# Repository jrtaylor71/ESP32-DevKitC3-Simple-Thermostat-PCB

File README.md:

# ESP32-S3-Simple-Thermostat

A comprehensive, feature-rich simple thermostat system built on the ESP32 platform with professional PCB design. Perfect for DIY smart home automation with full Home Assistant integration.

## 🌟 Key Features

- **📱 Local Touch Control**: ILI9341 TFT LCD with intuitive touch interface
- **🏠 Smart Home Ready**: Full MQTT integration with Home Assistant auto-discovery and climate entity support
- **📅 Bidirectional Schedule Sync**: 7-day schedules with day/night periods, HA helper automation, and live two-way update flow
- **🌡️ Multiple Sensors**: AHT20/BME280 ambient temperature and humidity plus DS18B20 hydronic water sensing
- **⚡ Multi-Stage HVAC**: Support for 2-stage heating and cooling, stage timing, delta thresholds, and stage 2 runtime logic
- **🌍 Regional HVAC Behavior**: Switchable US mode (standard temperature-driven cooling) or EU mode (adds optional humidity-driven dehumidification support alongside temperature control)
- **🔄 Heat Pump Ready**: Reversing valve support and heat-pump-compatible staging logic
- **🔥 Backup Heat Monitoring**: Auxiliary heat fallback logic with delay windows and temperature-drop detection
- **💨 Advanced Fan Control**: Auto, continuous, and scheduled cycling modes with independent heat/cool fan relay requirements
- **🔥 Separate Heat/Cool Fan Logic**: Configure whether the fan relay is needed for heating, cooling, or both for legacy HVAC systems
- **🧯 Hydronic Safety Protection**: DS18B20 water monitoring with lockout logic that blocks unsafe fan/heating operation and protects radiant systems
- **🚿 Shower Mode**: Pause heating for 5-120 minutes with countdown timer and buzzer alert
- **🌤️ Weather Integration**: OpenWeatherMap and Home Assistant weather with color-coded icons, current conditions, and display updates
- **🏢 Multi-Thermostat Support**: Scale from single-device installs to multi-device Home Assistant automation setups
- **🌐 Modern Web Interface**: Complete tabbed interface with embedded scheduling, status monitoring, OTA upload, and settings management
- **📡 Offline Operation**: Full functionality without WiFi connection or internet access
- **🔧 Professional PCB**: Custom PCB design for clean, permanent installation and compact integration
- **🔄 OTA Updates**: Over-the-air firmware updates with real-time progress tracking and reboot recovery
- **🔒 Factory Reset**: Built-in reset capability via boot button for clean default recovery
- **🎭 Motion Detection**: LD2410 24GHz mmWave sensor for automatic display wake and occupancy-aware screen behavior
- **🔊 Audible Alerts**: Buzzer feedback for shower mode, relay events, and user interaction cues
- **🧠 Reliability Features**: Watchdog reset, anti-flicker display refresh, I2C protection, and graceful sensor recovery

## �️ Operating Modes

### Thermostat Modes
- **Off**: All heating, cooling, and fan demand relays are disabled
- **Heat**: Single heat setpoint with configurable swing (hysteresis) to prevent short-cycling
- **Cool**: Single cool setpoint with configurable swing (hysteresis) to prevent short-cycling
- **Auto**: Single setpoint with a wider dead-zone swing; heating and cooling only activate once the temperature moves outside the dead-zone and turn off at the setpoint boundary rather than immediately on dead-zone re-entry

### Fan Modes
- **Auto**: Fan runs only when heating or cooling demand is active, based on the independent heat/cool fan relay requirement settings
- **On**: Fan runs continuously regardless of HVAC demand
- **Cycle**: Fan runs on a repeating schedule (configurable minutes per hour) even without active heating or cooling demand

### Regional HVAC Modes
- **US Mode**: Standard temperature-driven heating and cooling control
- **EU Mode**: Adds an optional humidity-driven dehumidification assist that runs alongside temperature control, using a configurable humidity setpoint, deadband, and dedicated relay selection

### Schedule Modes
- **Scheduled**: Setpoints automatically follow the active day/night period for the current day of week
- **Manual Override**: Adjusting a setpoint while a schedule is active temporarily overrides the schedule for a fixed duration before resuming normal scheduled behavior
- **Disabled**: Schedule following can be turned off entirely in favor of fixed manual setpoints

### Shower Mode
- Temporarily pauses heating for a configurable duration (5-120 minutes)
- Displays a live countdown timer on the touch screen while active
- Buzzer alert signals when the countdown is about to end
- Can be toggled directly from the touch screen setpoint control when enabled in settings

## �🚀 Quick Start

 - PCB V1.x

 - PCB V3.x

### Hardware Requirements
- ESP32-S3-WROOM-1-N16 (16MB Flash, No PSRAM) or N8/N32 variants
- ILI9341 320x240 TFT LCD with XPT2046 Touch Controller
- AHT20 or BME280 Temperature/Humidity Sensor (I2C)
- DS18B20 Temperature Sensor (optional, for hydronic heating)
- LD2410 24GHz mmWave Motion Sensor (optional, for display wake)
- 5x Relay Module for HVAC control
- Custom PCB that can use either onboard relay or external relays via pin header

### Software Setup

#### Option 1: Use Prebuilt Firmware (Recommended)
1. Clone this repository
2. Navigate to `firmware/` directory
3. Find the latest build folder (e.g., `build_YYYYMMDD-HHMMSS/`)
4. Flash using the variant-specific script:
   - **Linux/Mac**: 
     - Default: `./latest_flash_N16.sh` (uses /dev/ttyACM0)
     - Custom port: `./latest_flash_N16.sh /dev/ttyUSB0`
   - **Windows**: 
     - Default: `latest_flash_N16.bat` (uses COM3)
     - Custom port: `latest_flash_N16.bat COM4`
5. Use touch interface to configure WiFi and settings

#### Option 2: Build from Source
1. Install [PlatformIO](https://platformio.org/) IDE
2. Clone this repository
3. Open project in PlatformIO
4. Build firmware using `./build.sh` with options:
   - **Interactive mode**: `./build.sh` (select from menu)
   - **Specific variant**: `./build.sh 1` (N8), `./build.sh 2` (N16), or `./build.sh 3` (N32)
   - **All variants**: `./build.sh all` or `./build.sh 4`
   - **Additional flags**: `clean`, `quiet`, `cleanlibs`
   - **Examples**: 
     - `./build.sh 2` - Build 16MB variant (default)
     - `./build.sh all clean` - Clean build all variants
     - `./build.sh 3 quiet` - Build 32MB silently
     - `./build.sh cleanlibs` - Remove all libraries and packages
5. Memory usage: RAM 25.2% (82728/327680 bytes); Flash 19.0% (1246KB/6553KB for N16)
6. Firmware organized in `firmware/N8/`, `firmware/N16/`, `firmware/N32/` directories
7. Flash using variant-specific scripts:
   - **Linux/Mac**: 
     - Default: `./firmware/latest_flash_N16.sh` (uses /dev/ttyACM0)
     - Custom port: `./firmware/latest_flash_N16.sh /dev/ttyUSB0`
   - **Windows**: 
     - Default: `firmware\latest_flash_N16.bat` (uses COM3)
     - Custom port: `firmware\latest_flash_N16.bat COM5`
8. Use touch interface to configure WiFi and settings

#### Flashing Requirements
- **esptool.py** (installed automatically with PlatformIO)
- **USB connection** to ESP32-S3
- **Boot mode**: Hold BOOT button while connecting USB (if needed)
- **Default serial port**: `/dev/ttyACM0` (Linux/Mac) or `COM3` (Windows)

#### Manual Flashing with esptool

If you need to flash manually using esptool, use the following command:

**Linux/Mac:**
```bash
esptool.py --chip esp32s3 --port /dev/ttyACM0 --baud 460800 --before default_reset --after hard_reset write_flash -z \
    --flash_mode dio --flash_freq 80m --flash_size 16MB \
    0x0 bootloader.bin \
    0x8000 partitions.bin \
    0x10000 firmware.bin
```

**Windows:**
```bash
esptool.py --chip esp32s3 --port COM3 --baud 460800 --before default_reset --after hard_reset write_flash -z \
    --flash_mode dio --flash_freq 80m --flash_size 16MB \
    0x0 bootloader.bin \
    0x8000 partitions.bin \
    0x10000 firmware.bin
```

**Flash addresses for the 3 required files:**
- `bootloader.bin` at address `0x0`
- `partitions.bin` at address `0x8000`
- `firmware.bin` at address `0x10000`

**Adjust for your hardware:**
- Change `--port` to your serial port (Linux: `/dev/ttyACM0` or `/dev/ttyUSB0`, Windows: `COM3`, `COM4`, etc.)
- Change `--flash_size` to `8MB`, `16MB`, or `32MB` to match your ESP32-S3 variant (N8, N16, or N32)

For detailed build and flash instructions, see [USER_MANUAL.md](USER_MANUAL.md)

## 💻 Web Interface

Access the thermostat's web interface by navigating to its IP address:

### Tabbed Interface with Embedded Features

**Status Tab**: Real-time monitoring of:
- Current temperature and humidity
- Thermostat and fan modes
- Relay states and system status
- Weather information (when configured)
- Barometric pressure (with BME280 sensor)

**Settings Tab**: Complete configuration interface for:

- Temperature setpoints and control modes
- MQTT/Home Assistant integration and broker settings
- WiFi network settings and reboot recovery
- Multi-stage HVAC parameters including stage 2 runtime and delta thresholds
- Reversing valve configuration for heat-pump systems
- Backup heat enablement, relay selection, delay timing, and temperature-drop logic
- Hydronic heating controls with low/high water protection thresholds
- Fan scheduling options and independent heat/cool fan relay toggles
- Regional HVAC mode selection for US or EU behavior
- EU humidity dehumidification controls, relay selection, setpoint, and deadband
- Shower mode enable/disable and duration (5-120 minutes)
- Display brightness, sleep, and clock settings
- Temperature/humidity sensor calibration and offsets
- OTA update management and firmware details

**Schedule Tab**: Comprehensive 7-day scheduling:
- Day and night periods for each day of the week
- Editable Heat, Cool, and Auto temperatures for each period
- Time controls for period transitions
- Schedule enable/disable and override controls
- All options always visible - no hidden menus

**Weather Tab**: Weather data configuration:
- OpenWeatherMap API integration
- Home Assistant weather entity integration
- Configurable update intervals (5-60 minutes)
- City/state/country configuration

**System Tab**: Device information and firmware updates:
- System information and uptime
- Firmware version details
- OTA firmware upload with progress tracking
- Reboot and factory reset options

For complete usage instructions, see [USER_MANUAL.md](USER_MANUAL.md)

## 🏠 Home Assistant Integration

### Automatic Discovery & Control
Automatic discovery and integration with Home Assistant:

1. Enable MQTT in thermostat settings
2. Configure MQTT broker details
3. Thermostat appears automatically in Home Assistant with a full climate entity and status payloads
4. Full control via Home Assistant interface
5. Supports climate entity with heating, cooling, auto, and off modes
6. Publishes relay, mode, target, schedule override, and hydronic state for automation use

### Bidirectional Schedule Sync 🔄
Full synchronization between thermostat and Home Assistant:

**Device → HA (Inbound)**: 
- Thermostat publishes complete schedule on boot and config changes
- HA automations automatically update helper entities for each day and period
- Changes made on device instantly visible in HA

**HA → Device (Outbound)**:
- Change any schedule helper in HA (time, temperature, enabled status)
- Automation publishes change to device via MQTT immediately
- Device receives and applies change instantly
- No manual sync needed - fully automatic bidirectional flow

**Multi-Thermostat Support**:
- Each device gets its own set of helpers (shop_thermostat, studio_thermostat, house_thermostat, etc.)
- Centralized multi-device automation handles all thermostats
- Proper hostname normalization for MQTT topics vs. helper IDs
- Can manage 10+ thermostats from single HA instance

**Setup Instructions**:
1. Ensure MQTT is enabled on thermostat
2. Copy `multi_thermostat_schedule_sync.yaml` to HA packages directory
3. Generate per-device packages: `./generate_schedule_package.sh shop_thermostat`
4. Add package to HA configuration
5. Reload automations/scripts in HA
6. Helpers auto-populate from device schedule state

## 🛠️ Advanced Features

### Multi-Stage Operation
- Intelligent staging based on time and temperature
- Configurable stage 2 activation parameters and runtime thresholds
- Prevents system short-cycling and optimizes energy efficiency
- Supports separate heating and cooling stage logic for multi-stage HVAC systems
- Includes runtime gating and dead-zone control behavior for stable operation

### US/EU Regional HVAC Behavior
- Thermostat region mode can be configured for US or EU control behavior
- **US Mode**: Standard temperature-driven heating and cooling control
- **EU Mode**: Adds optional humidity-driven dehumidification assist that runs alongside temperature control, with configurable setpoint and deadband
- Standalone dehumidification state is surfaced to web status and TFT display
- Works with relay selection modes for cooling stage 1, stage 2, or pump relay output

### Heat Pump and Backup Heat Support
- Reversing valve support for heat-pump systems with mode-aware valve control
- Backup heat logic can monitor a primary heat source and automatically add auxiliary heat when recovery stalls or temperature falls too quickly
- Relay conflicts are automatically managed so backup heat does not overlap with reserved stage 2 or reversing valve outputs
- Works alongside standard heating and cooling staging without forcing a single control strategy

### Hydronic Heating Support
- DS18B20 water temperature monitoring
- Safety interlocks prevent operation when water is too cold
- Configurable high/low temperature thresholds
- Hydronic lockout logic blocks unsafe heating/fan behavior when the loop is below the configured minimum
- Perfect for radiant floor heating systems and hydronic boiler setups

### Fan Control Options
- **Auto**: Fan runs only with heating/cooling
- **On**: Continuous fan operation
- **Cycle**: Scheduled fan operation (configurable minutes per hour)
- **Independent Heat/Cool Relay Settings**: Choose whether a fan relay is required while heating, while cooling, or for both modes
- **Legacy HVAC Compatibility**: Supports systems where the fan is required for cooling only, heating only, or both without forcing a single global setting

### Display, Sensor, and Safety Enhancements
- Motion-based wake on LD2410 radar occupancy detection
- Display sleep and dimming support with activity sensing
- Buzzer feedback for alerts, boot tones, and mode transitions
- Watchdog protection, OTA recovery, and factory reset support
- AHT20/BME280 temperature/humidity calibration offsets and sensor error recovery
- I2C mutex protection to prevent bus contention between sensors and display logic
- Anti-flicker display refresh logic and stable UI updates
- Hydronic low-temp alert publishing and lockout recovery monitoring for radiant systems

### Included Hardware and Support Features
- 5 relay outputs for heating, cooling, and fan control
- Optional DS18B20 hydronic sensor and LD2410 motion sensor
- Local TFT UI with touch controls and embedded settings
- Web interface for complete configuration and status polling
- OTA firmware upload through the device’s system tab
- Compatibility with both single-device and multi-thermostat Home Assistant installations

## 🖨️ 3D Printable Case

A professional two-part case design is included for clean wall-mount installation:

### Case Features
- **Two-part screw-retained design**: Front (display side) and back (wall-mount side) halves
- **Integrated PCB mounting**: Built-in standoffs (13mm height) for secure PCB installation
- **Countersunk front screws**: 4× M2.5 countersunk (DIN 7991), 10–12mm length, 7mm inset
- **Keyhole wall mounting**: Easy installation without removing case (83mm spacing)
- **Display opening**: Precise 50mm × 68mm opening for 3.2" ILI9341 touchscreen (rotated 90°)
- **AHT20 sensor + LDR cutouts**: 12.5×6mm rectangle (rotated 90°) and Ø5.5mm hole
- **Wire management**: 22mm back pass-through plus side ventilation slots
- **Ventilation**: Strategically placed slots for optimal heat dissipation
- **Professional finish**: Smooth surfaces and rounded edges

### Files Included
- `case/freecad_front_case.py` - Front case (display side) FreeCAD Python script
- `case/freecad_back_case.py` - Back case (wall-mount side) FreeCAD Python script
- `case/freecad_outputs/front_case_display_freecad.stl` - Front half for 3D printing
- `case/freecad_outputs/back_case_wall_freecad.stl` - Back half for 3D printing
- `case/freecad_outputs/front_case_display_freecad.FCStd` - Front case FreeCAD project
- `case/freecad_outputs/back_case_wall_freecad.FCStd` - Back case FreeCAD project
- `case/freecad_outputs/front_case_display_freecad.step` - Front case STEP format
- `case/freecad_outputs/back_case_wall_freecad.step` - Back case STEP format
- `case/freecad_outputs/CE5_front_case_display_freecad.gcode` - Creality Ender 5 gcode (front)
- `case/freecad_outputs/CE5_back_case_wall_freecad.gcode` - Creality Ender 5 gcode (back)

### Print Specifications
- **Material**: PLA or PETG recommended
- **Layer height**: 0.2mm
- **Infill**: 15-20%
- **Supports**: None required
- **Print time**: ~7–9 hours total
- **Dimensions**: 149.0mm × 105.5mm × ~47mm (assembled)
  - Front: ~17.1mm (2.5mm wall; 13mm standoffs; front walls 1.6mm above standoffs)
  - Back: ~30.1mm (2.5mm wall; 20mm component clearance; bosses/keyholes)

**STL Files Location**: All printable STL files are in the `case/freecad_outputs/` directory.

### Motion Detection
- **LD2410 24GHz mmWave Sensor**: Automatic display wake on motion detection
- **Hardware Pins**: RX=15, TX=16, Motion=18
- **Robust Detection**: Works with sensors that don't respond to UART commands
- **Home Assistant Integration**: Motion sensor auto-discovery and status publishing
- **Energy Saving**: Display automatically sleeps when no motion detected
- **Seamless Operation**: Works alongside existing touch controls

### Safety Features
- Watchdog timer prevents system lockups
- Factory reset via boot button (10+ seconds)
- Temperature limit enforcement
- Graceful offline operation

## 🔧 Factory Reset

Press and hold the boot button for more than 10 seconds while the thermostat is running to restore all settings to defaults.

## 📄 License

This project is released under the GNU General Public License v3.0. Free to use, modify, and distribute. NOT for commercial use.

## 🤝 Contributing

Contributions welcome! Please:
1. Fork the repository
2. Create a feature branch
3. Make your changes
4. Submit a pull request

## 📞 Support

- **Issues**: Use GitHub Issues for bug reports
- **Discussions**: GitHub Discussions for questions
- **Documentation**: Comprehensive docs included
- **Serial Debug**: Detailed logging at 115200 baud

## 🙏 Credits & Acknowledgments

**Firmware**: Jonn Taylor - Enhanced firmware implementation

**Created for the DIY smart home community**

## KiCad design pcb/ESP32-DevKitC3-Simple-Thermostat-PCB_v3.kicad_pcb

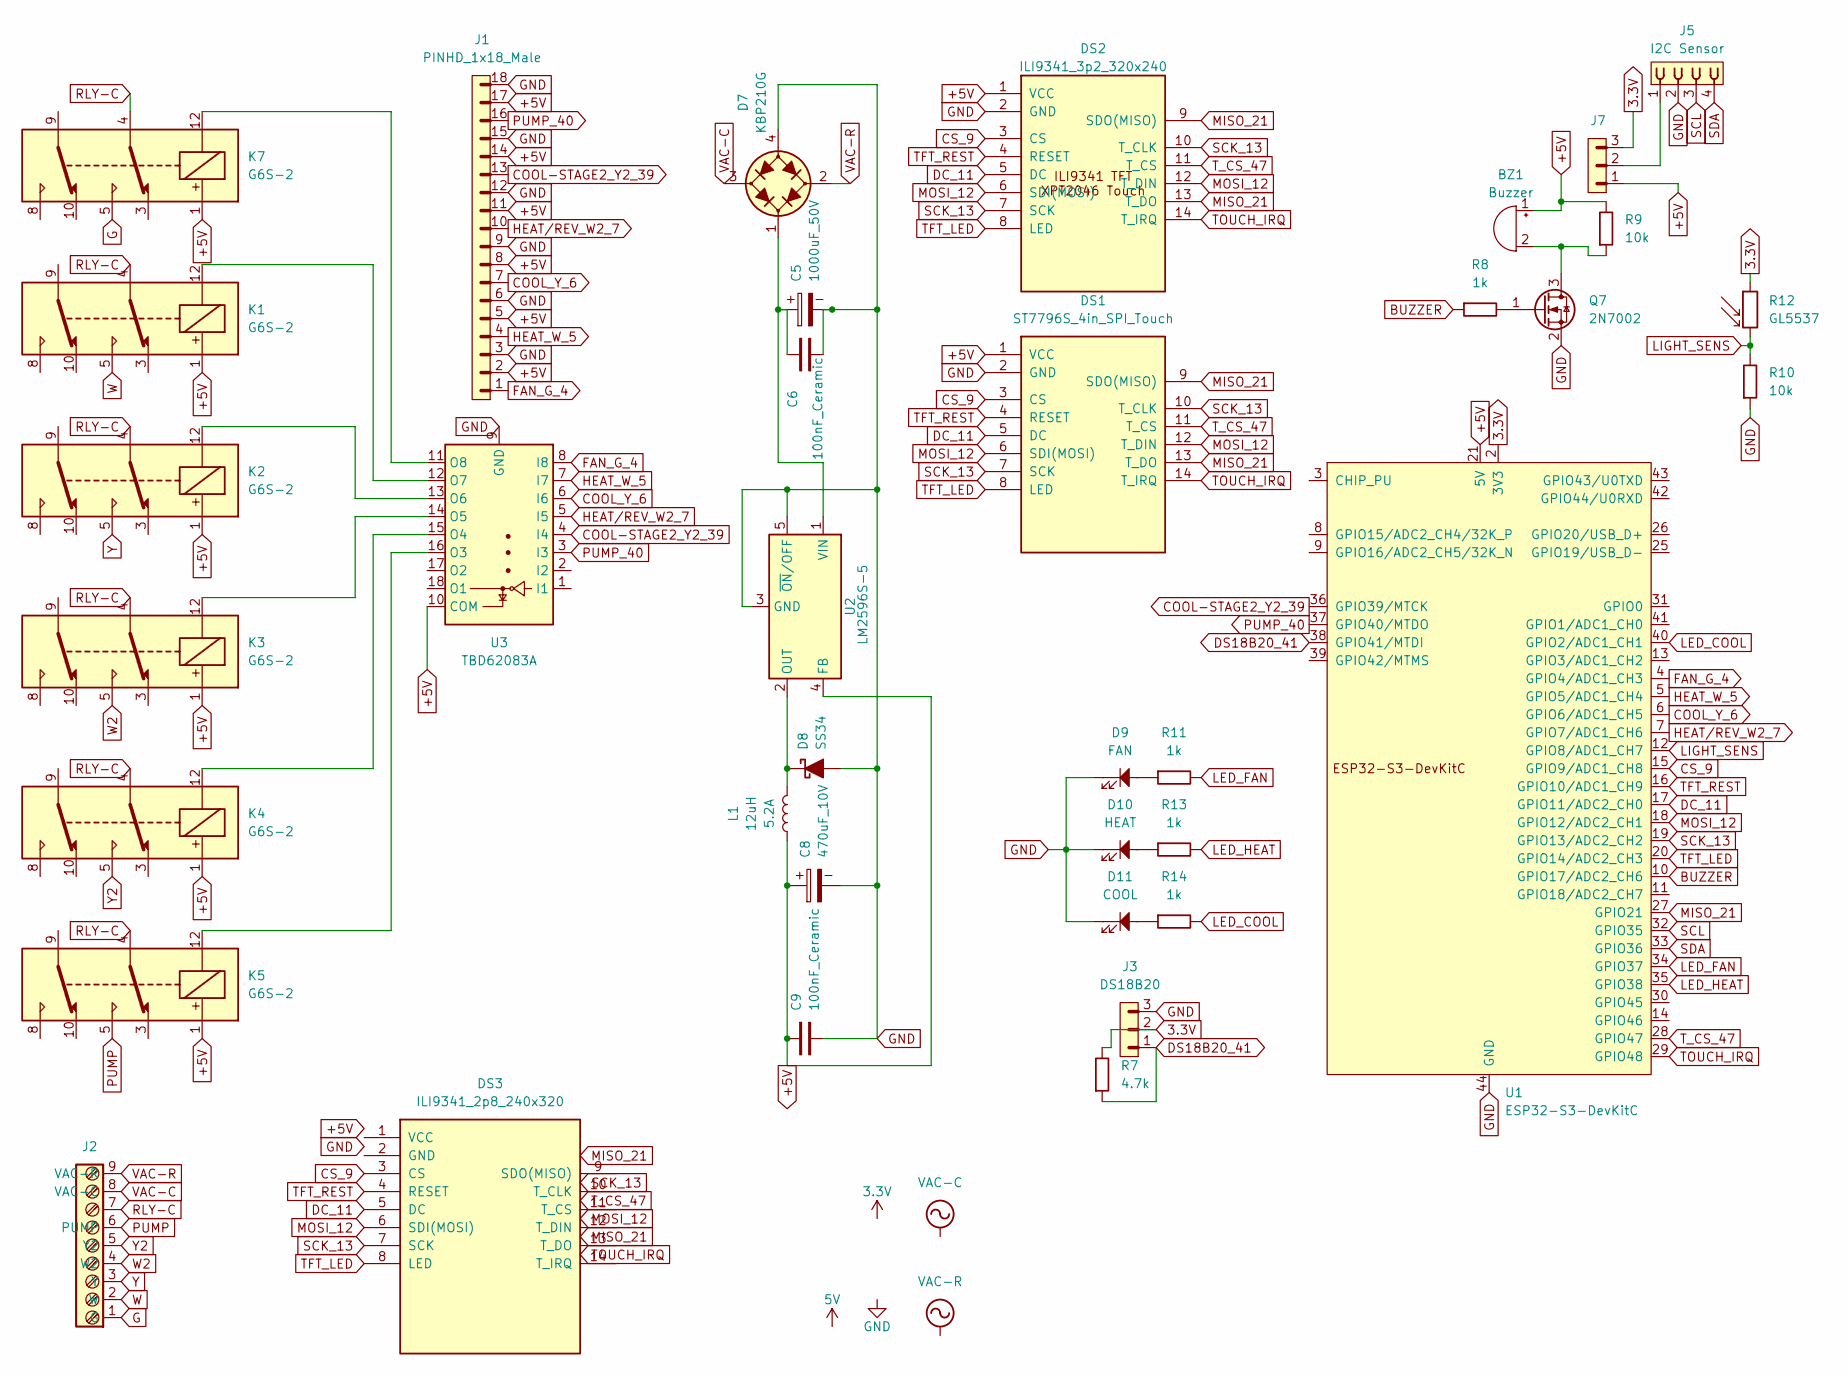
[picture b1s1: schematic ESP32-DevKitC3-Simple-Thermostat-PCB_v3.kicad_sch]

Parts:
BZ1: Buzzer; Buzzer_TDK_PS1240P02BT_D12.2mm_H6.5mm; LCSC C76871
C5: 1000uF_50V; CP_Radial_D16.0mm_P7.50mm; LCSC C445418
C6, C9: 100nF_Ceramic; C_Disc_D5.0mm_W2.5mm_P2.50mm; LCSC C1517817
C8: 470uF_10V; CP_Radial_D8.0mm_P3.50mm; LCSC C3274796
D7: KBP210G; Diode_Bridge_KBP; LCSC C244333
D8: SS34; D_SMC; LCSC C908239
D9: FAN; LED_D3.0mm; LCSC C17340814
D10: HEAT; LED_D3.0mm; LCSC C5990731
D11: COOL; LED_D3.0mm; LCSC C17304835
DS1: ST7796S_4in_SPI_Touch; ST7796S_4in_SPI_Touch_Module_14P
DS2: ILI9341_3p2_320x240
DS3: ILI9341_2p8_240x320
J1: PINHD_1x18_Male; PinHeader_1x18_P2.54mm_Vertical; LCSC C27985197
J2: Screw_Terminal_9_P3.50mm; TerminalBlock_Phoenix_PT-1,5-9-3.5-H_1x09_P3.50mm_Horizontal; LCSC C6373199
J3: DS18B20; PinHeader_1x03_P2.54mm_Vertical; LCSC C2932698
J5: I2C Sensor; PinSocket_1x04_P2.54mm_Vertical
J7: PINHD_1x3_Male; PinHeader_1x03_P2.54mm_Vertical; LCSC C2932698
K1, K2, K3, K4, K5, K7: G6S-2; Relay_DPDT_Omron_G6S-2
L1: 12uH_5.2A_1260; L_Bourns_SRR1260; Part Number SRR1260-120M; LCSC C2041353
Q7: 2N7002; SOT-23; LCSC C8545
R7: 4.7k; R_Axial_DIN0207_L6.3mm_D2.5mm_P10.16mm_Horizontal; LCSC C119339
R8, R11, R13, R14: 1k; R_Axial_DIN0207_L6.3mm_D2.5mm_P10.16mm_Horizontal; LCSC C119324
R9, R10: 10k; R_Axial_DIN0207_L6.3mm_D2.5mm_P10.16mm_Horizontal; LCSC C119347
R12: GL5537; R_LDR_5.1x4.3mm_P3.4mm_Vertical; LCSC C125628
U1: ESP32-S3-DevKitC
U2: LM2596S-5; TO-263-5_TabPin3; LCSC C347445
U3: TBD62083A; DW18

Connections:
3.3V: J3.2, J7.3, R7.2, R12.1, U1.1 (3V3), U1.2 (3V3)
+5V: BZ1.1 (+), C8.1, C9.1, DS1.1 (VCC), DS2.1 (VCC), J1.2, J1.5, J1.8, J1.11, J1.14, J1.17, J7.1, K1.1, K2.1, K3.1, K4.1, K5.1, K7.1, L1.1, R9.2, U1.21 (5V), U2.4 (FB), U3.10 (COM)
BUZZER: R8.1, U1.10 (GPIO17/ADC2_CH6)
COOL-STAGE2_Y2_39: J1.13, U1.36 (GPIO39/MTCK), U3.4 (I4)
COOL_Y_6: J1.7, U1.6 (GPIO6/ADC1_CH5), U3.6 (I6)
CS_9: DS1.3 (CS), DS2.3 (CS), DS3.3 (CS), U1.15 (GPIO9/ADC1_CH8)
DC_11: DS1.5 (DC), DS2.5 (DC), DS3.5 (DC), U1.17 (GPIO11/ADC2_CH0)
DS18B20_41: J3.1, R7.1, U1.38 (GPIO41/MTDI)
FAN_G_4: J1.1, U1.4 (GPIO4/ADC1_CH3), U3.8 (I8)
G: J2.1 (G), K7.5
GND: C5.2, C6.1, C8.2, C9.2, D7.4 (-), D8.2 (A), D9.1, D10.1, D11.1, DS1.2 (GND), DS2.2 (GND), J1.3, J1.6, J1.9, J1.12, J1.15, J1.18, J3.3, J5.2, Q7.2 (S), R10.1, U1.22 (GND), U1.23 (GND), U1.24 (GND), U1.44 (GND), U2.3 (GND), U2.5 (~ON/OFF), U3.9 (GND); also elsewhere on the board
HEAT_W_5: J1.4, U1.5 (GPIO5/ADC1_CH4), U3.7 (I7)
HEAT/REV_W2_7: J1.10, U1.7 (GPIO7/ADC1_CH6), U3.5 (I5)
LED_COOL: R14.2, U1.40 (GPIO2/ADC1_CH1)
LED_FAN: R11.2, U1.34 (GPIO37)
LED_HEAT: R13.2, U1.35 (GPIO38)
LIGHT_SENS: R10.2, R12.2, U1.12 (GPIO8/ADC1_CH7)
MISO_21: DS1.9 (SDO(MISO)), DS1.13 (T_DO), DS2.9 (SDO(MISO)), DS2.13 (T_DO), U1.27 (GPIO21)
MOSI_12: DS1.6 (SDI(MOSI)), DS1.12 (T_DIN), DS2.6 (SDI(MOSI)), DS2.12 (T_DIN), DS3.6 (SDI(MOSI)), U1.18 (GPIO12/ADC2_CH1)
unnamed: BZ1.2 (-), Q7.3 (D), R9.1
unnamed: C5.1, C6.2, D7.1 (+), U2.1 (VIN)
unnamed: D8.1 (K), L1.2, U2.2 (OUT)
unnamed: D9.2, R11.1
unnamed: D10.2, R13.1
unnamed: D11.2, R14.1
unnamed: J5.1, J7.2
unnamed: Q7.1 (G), R8.2
unnamed: K5.12, U3.16 (O3)
unnamed: K4.12, U3.15 (O4)
unnamed: K3.12, U3.14 (O5)
unnamed: K2.12, U3.13 (O6)
unnamed: K1.12, U3.12 (O7)
unnamed: K7.12, U3.11 (O8)
PUMP: J2.6 (PUMP), K5.5
PUMP_40: J1.16, U1.37 (GPIO40/MTDO), U3.3 (I3)
RLY-C: J2.7, K1.4, K2.4, K3.4, K4.4, K5.4, K7.4
SCK_13: DS1.7 (SCK), DS1.10 (T_CLK), DS2.7 (SCK), DS2.10 (T_CLK), DS3.7 (SCK), U1.19 (GPIO13/ADC2_CH2)
SCL: J5.3, U1.32 (GPIO35)
SDA: J5.4, U1.33 (GPIO36)
TFT_LED: DS1.8 (LED), DS2.8 (LED), DS3.8 (LED), U1.20 (GPIO14/ADC2_CH3)
TFT_REST: DS1.4 (RESET), DS2.4 (RESET), DS3.4 (RESET), U1.16 (GPIO10/ADC1_CH9)
TOUCH_IRQ: DS1.14 (T_IRQ), DS2.14 (T_IRQ), U1.29 (GPIO48)
T_CS_47: DS1.11 (T_CS), DS2.11 (T_CS), U1.28 (GPIO47)
VAC-C: D7.3 (2), J2.8 (VAC-C)
VAC-R: D7.2 (1), J2.9 (VAC-R)
W: J2.2 (W), K1.5
W2: J2.4 (W2), K3.5
Y: J2.3 (Y), K2.5
Y2: J2.5 (Y2), K4.5

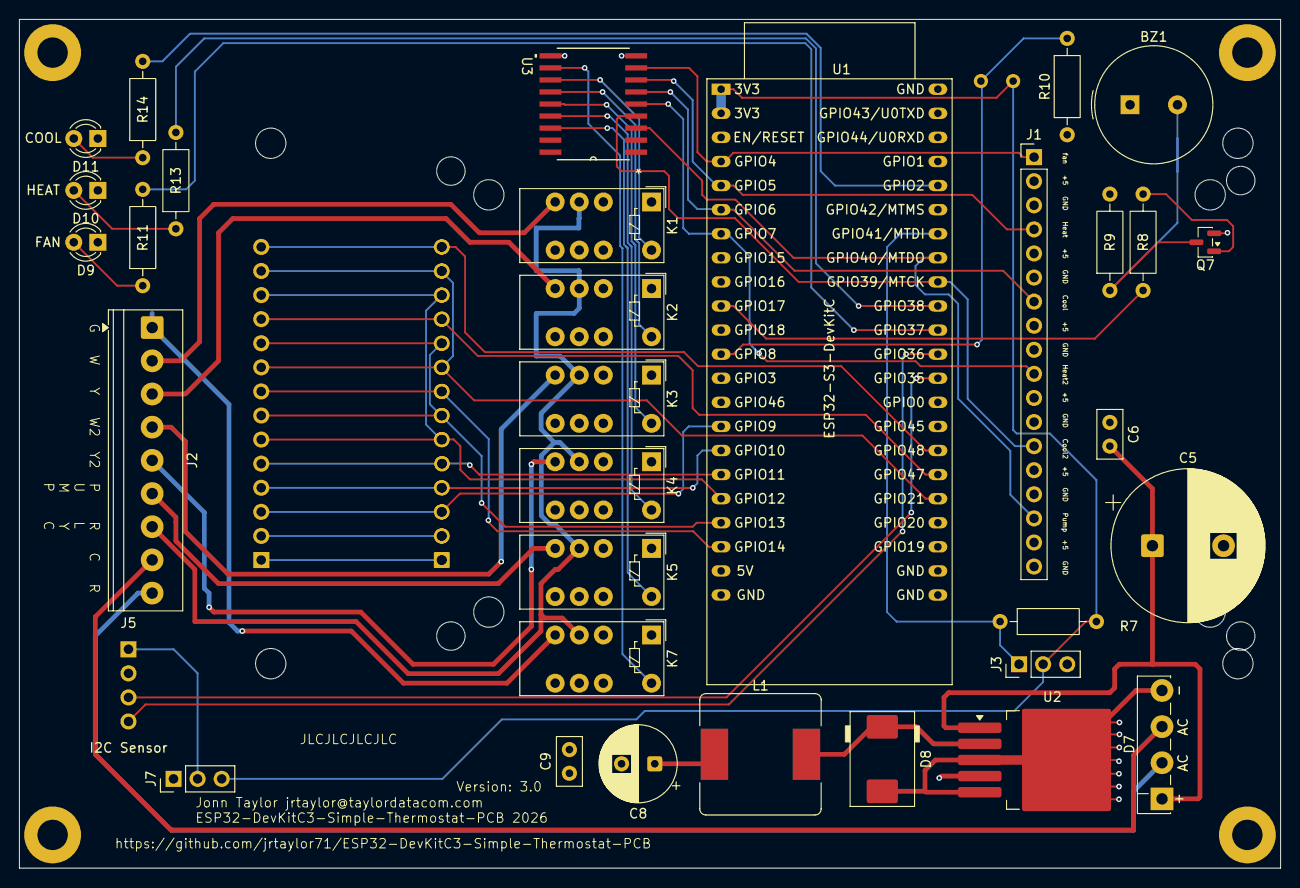
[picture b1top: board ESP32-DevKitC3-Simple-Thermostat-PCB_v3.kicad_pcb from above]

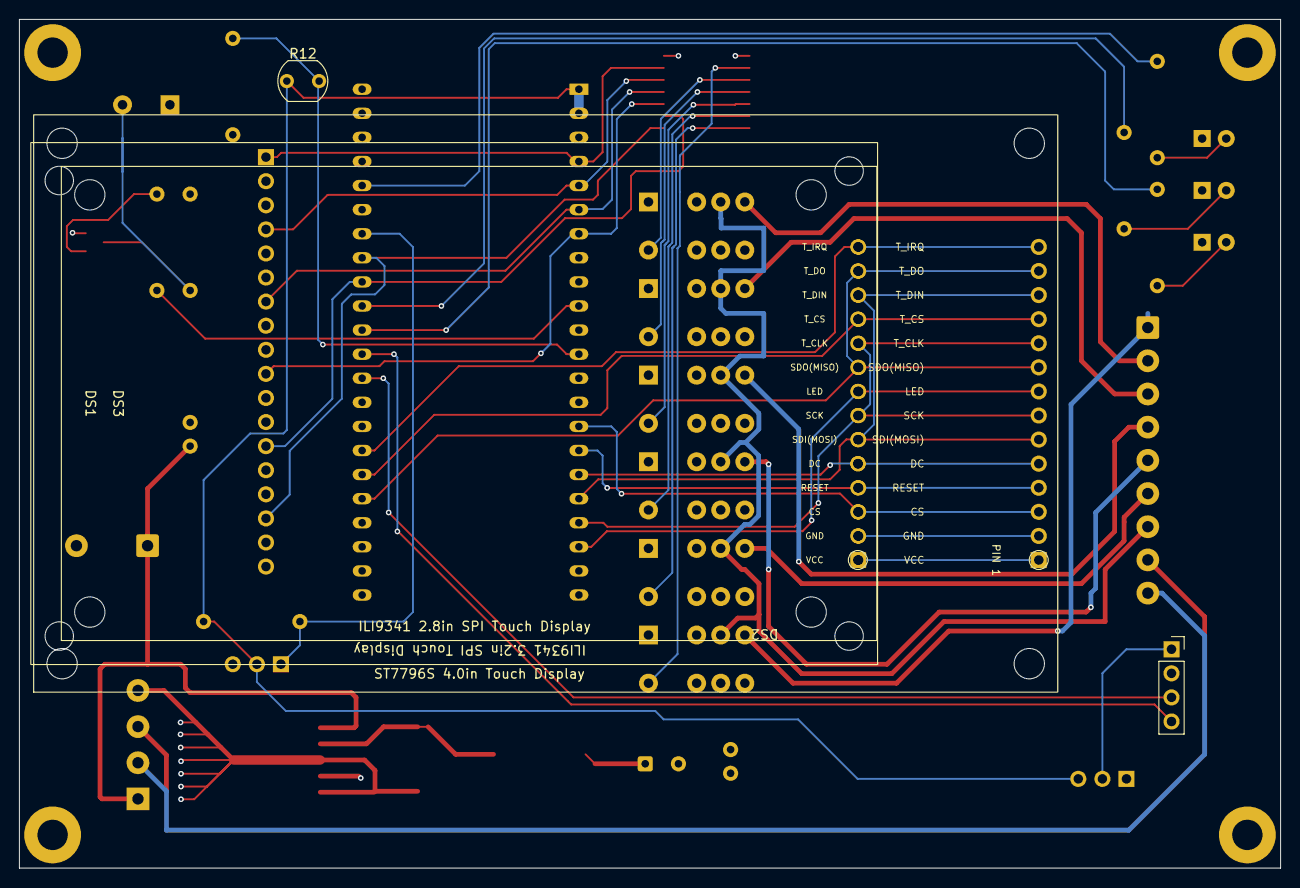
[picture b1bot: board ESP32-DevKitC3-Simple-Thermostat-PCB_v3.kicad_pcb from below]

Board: 4 copper layers, 133.0 x 89.5 mm, 41 parts (5 on the bottom side), 49 nets.

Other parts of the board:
H1, H2, H3, H4: MountingHole_M3_3.2mm_Pad; MountingHole_3.2mm_Pad

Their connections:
GND: H1.1, H2.1, H3.1, H4.1; also elsewhere on the board

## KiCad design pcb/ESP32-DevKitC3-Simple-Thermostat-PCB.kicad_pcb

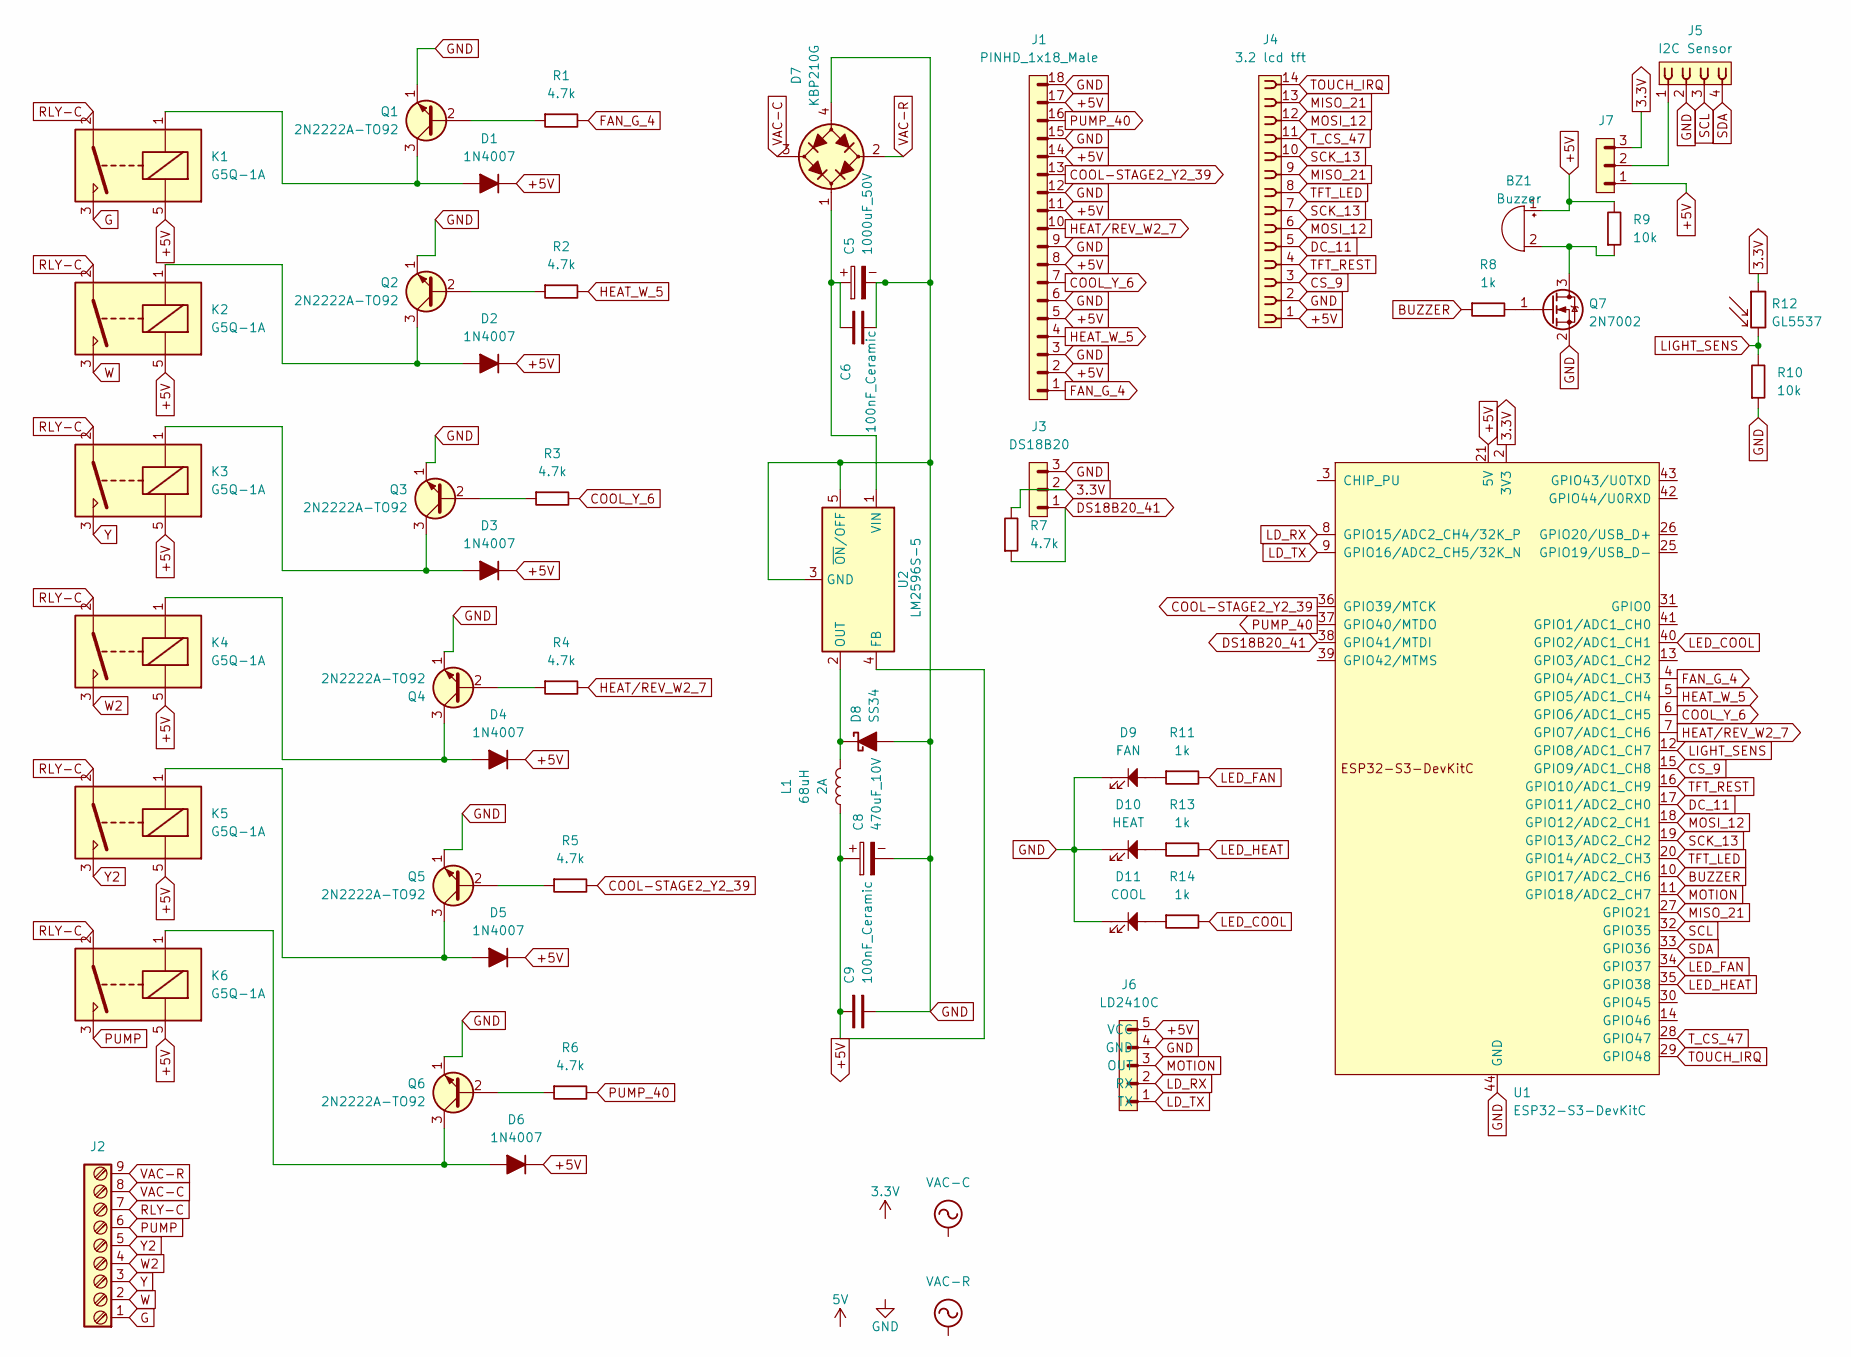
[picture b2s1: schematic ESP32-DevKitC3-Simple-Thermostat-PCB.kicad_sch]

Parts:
BZ1: Buzzer; Buzzer_TDK_PS1240P02BT_D12.2mm_H6.5mm
C5: 1000uF_50V; CP_Radial_D16.0mm_P7.50mm
C6, C9: 100nF_Ceramic; C_Disc_D5.0mm_W2.5mm_P2.50mm
C8: 470uF_10V; CP_Radial_D8.0mm_P3.50mm
D1, D2, D3, D4, D5, D6: 1N4007; D_DO-41_SOD81_P7.62mm_Horizontal
D7: KBP210G; Diode_Bridge_KBP
D8: SS34; D_SMC
D9: FAN; LED_D3.0mm
D10: HEAT; LED_D3.0mm
D11: COOL; LED_D3.0mm
J1: PINHD_1x18_Male; PinHeader_1x18_P2.54mm_Vertical
J2: Screw_Terminal_9_P3.50mm; TerminalBlock_Phoenix_PT-1,5-9-3.5-H_1x09_P3.50mm_Horizontal
J3: DS18B20; PinHeader_1x03_P2.54mm_Vertical
J4: 3.2 lcd tft; PinSocket_1x14_P2.54mm_Vertical
J5: I2C Sensor; PinSocket_1x04_P2.54mm_Vertical
J6: LD2410C; PinHeader_1x05_P2.54mm_Vertical
J7: PINHD_1x3_Male; PinHeader_1x03_P2.54mm_Vertical
K1, K2, K3, K4, K5, K6: G5Q-1A; Relay_SPST_Omron-G5Q-1A
L1: 12uH_5.2A_1260; L_Bourns_SRR1260; Part Number SRR1260-120M
Q1, Q2, Q3, Q4, Q5, Q6: 2N2222A-TO92; TO-92_Inline_Wide_EBC
Q7: 2N7002; SOT-23; LCSC C8545
R1, R2, R3, R4, R5, R6, R7: 4.7k; R_Axial_DIN0207_L6.3mm_D2.5mm_P10.16mm_Horizontal
R8, R11, R13, R14: 1k; R_Axial_DIN0207_L6.3mm_D2.5mm_P10.16mm_Horizontal
R9, R10: 10k; R_Axial_DIN0207_L6.3mm_D2.5mm_P10.16mm_Horizontal
R12: GL5537; R_LDR_5.1x4.3mm_P3.4mm_Vertical
U1: ESP32-S3-DevKitC
U2: LM2596S-5; TO-263-5_TabPin3

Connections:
3.3V: J3.2, J7.3, R7.2, R12.1, U1.1 (3V3), U1.2 (3V3)
+5V: BZ1.1 (-), C8.1, C9.1, D1.1 (K), D2.1 (K), D3.1 (K), D4.1 (K), D5.1 (K), D6.1 (K), J1.2, J1.5, J1.8, J1.11, J1.14, J1.17, J4.1, J6.5 (VCC), J7.1, K1.5, K2.5, K3.5, K4.5, K5.5, K6.5, L1.1, R9.2, U1.21 (5V), U2.4 (FB)
BUZZER: R8.1, U1.10 (GPIO17/ADC2_CH6)
COOL-STAGE2_Y2_39: J1.13, R5.2, U1.36 (GPIO39/MTCK)
COOL_Y_6: J1.7, R3.2, U1.6 (GPIO6/ADC1_CH5)
CS_9: J4.3, U1.15 (GPIO9/ADC1_CH8)
DC_11: J4.5, U1.17 (GPIO11/ADC2_CH0)
DS18B20_41: J3.1, R7.1, U1.38 (GPIO41/MTDI)
FAN_G_4: J1.1, R1.2, U1.4 (GPIO4/ADC1_CH3)
G: J2.1, K1.3
GND: C5.2, C6.1, C8.2, C9.2, D7.4 (-), D8.2 (A), D9.1, D10.1, D11.1, J1.3, J1.6, J1.9, J1.12, J1.15, J1.18, J3.3, J4.2, J5.2, J6.4 (GND), Q1.1 (E), Q2.1 (E), Q3.1 (E), Q4.1 (E), Q5.1 (E), Q6.1 (E), Q7.2 (S), R10.1, U1.22 (GND), U1.23 (GND), U1.24 (GND), U1.44 (GND), U2.3 (GND), U2.5 (~ON/OFF); also elsewhere on the board
HEAT_W_5: J1.4, R2.2, U1.5 (GPIO5/ADC1_CH4)
HEAT/REV_W2_7: J1.10, R4.2, U1.7 (GPIO7/ADC1_CH6)
LD_RX: J6.2 (RX), U1.8 (GPIO15/ADC2_CH4/32K_P)
LD_TX: J6.1 (TX), U1.9 (GPIO16/ADC2_CH5/32K_N)
LED_COOL: R14.2, U1.40 (GPIO2/ADC1_CH1)
LED_FAN: R11.2, U1.34 (GPIO37)
LED_HEAT: R13.2, U1.35 (GPIO38)
LIGHT_SENS: R10.2, R12.2, U1.12 (GPIO8/ADC1_CH7)
MISO_21: J4.9, J4.13, U1.27 (GPIO21)
MOSI_12: J4.6, J4.12, U1.18 (GPIO12/ADC2_CH1)
MOTION: J6.3 (OUT), U1.11 (GPIO18/ADC2_CH7)
unnamed: BZ1.2 (+), Q7.3 (D), R9.1
unnamed: D1.2 (A), K1.1, Q1.3 (C)
unnamed: D2.2 (A), K2.1, Q2.3 (C)
unnamed: D3.2 (A), K3.1, Q3.3 (C)
unnamed: D4.2 (A), K4.1, Q4.3 (C)
unnamed: D5.2 (A), K5.1, Q5.3 (C)
unnamed: D6.2 (A), K6.1, Q6.3 (C)
unnamed: C5.1, C6.2, D7.1 (+), U2.1 (VIN)
unnamed: D8.1 (K), L1.2, U2.2 (OUT)
unnamed: D9.2, R11.1
unnamed: D10.2, R13.1
unnamed: D11.2, R14.1
unnamed: J5.1, J7.2
unnamed: Q1.2 (B), R1.1
unnamed: Q2.2 (B), R2.1
unnamed: Q3.2 (B), R3.1
unnamed: Q4.2 (B), R4.1
unnamed: Q5.2 (B), R5.1
unnamed: Q6.2 (B), R6.1
unnamed: Q7.1 (G), R8.2
PUMP: J2.6, K6.3
PUMP_40: J1.16, R6.2, U1.37 (GPIO40/MTDO)
RLY-C: J2.7, K1.2, K2.2, K3.2, K4.2, K5.2, K6.2
SCK_13: J4.7, J4.10, U1.19 (GPIO13/ADC2_CH2)
SCL: J5.3, U1.32 (GPIO35)
SDA: J5.4, U1.33 (GPIO36)
TFT_LED: J4.8, U1.20 (GPIO14/ADC2_CH3)
TFT_REST: J4.4, U1.16 (GPIO10/ADC1_CH9)
TOUCH_IRQ: J4.14, U1.29 (GPIO48)
T_CS_47: J4.11, U1.28 (GPIO47)
VAC-C: D7.3 (2), J2.8
VAC-R: D7.2 (1), J2.9
W: J2.2, K2.3
W2: J2.4, K4.3
Y: J2.3, K3.3
Y2: J2.5, K5.3

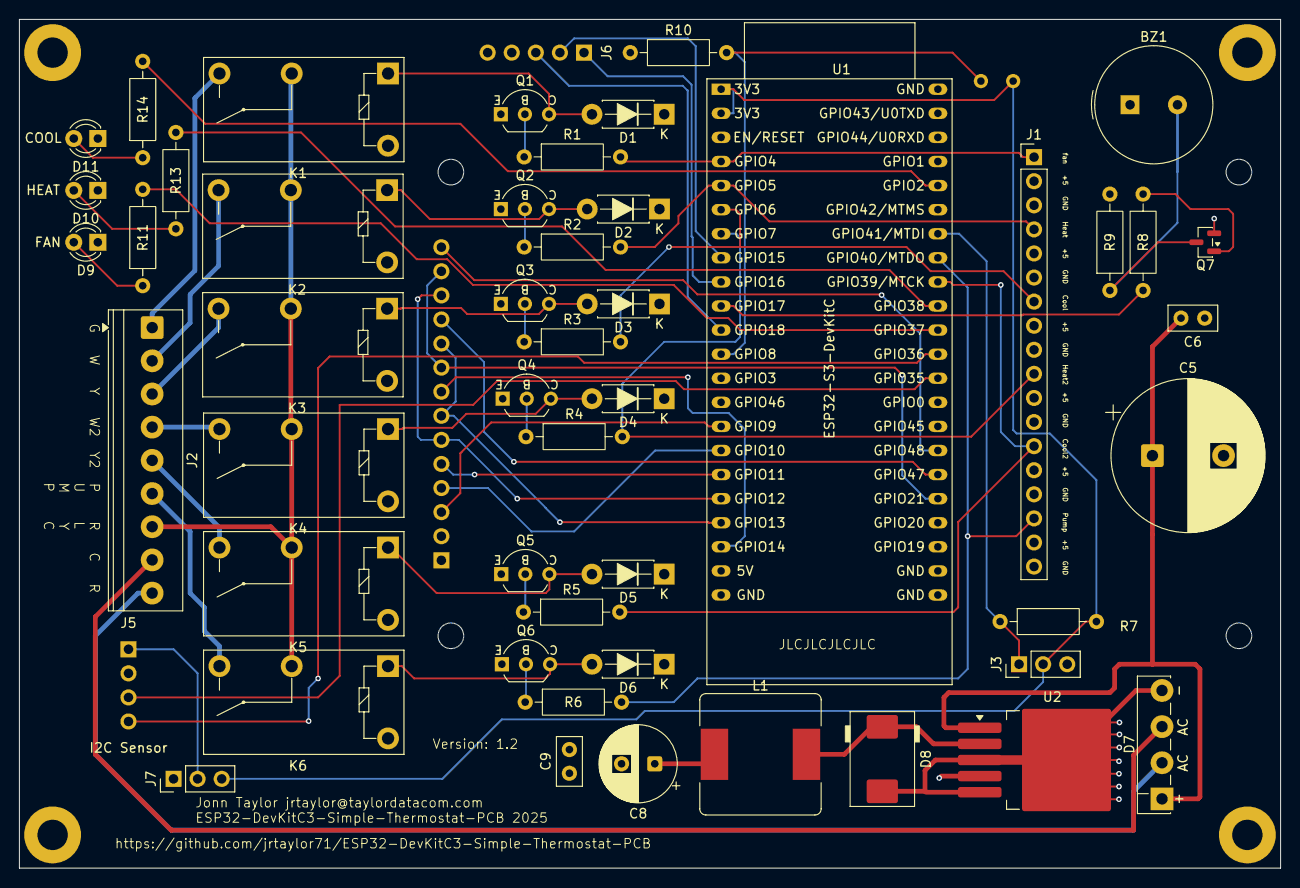
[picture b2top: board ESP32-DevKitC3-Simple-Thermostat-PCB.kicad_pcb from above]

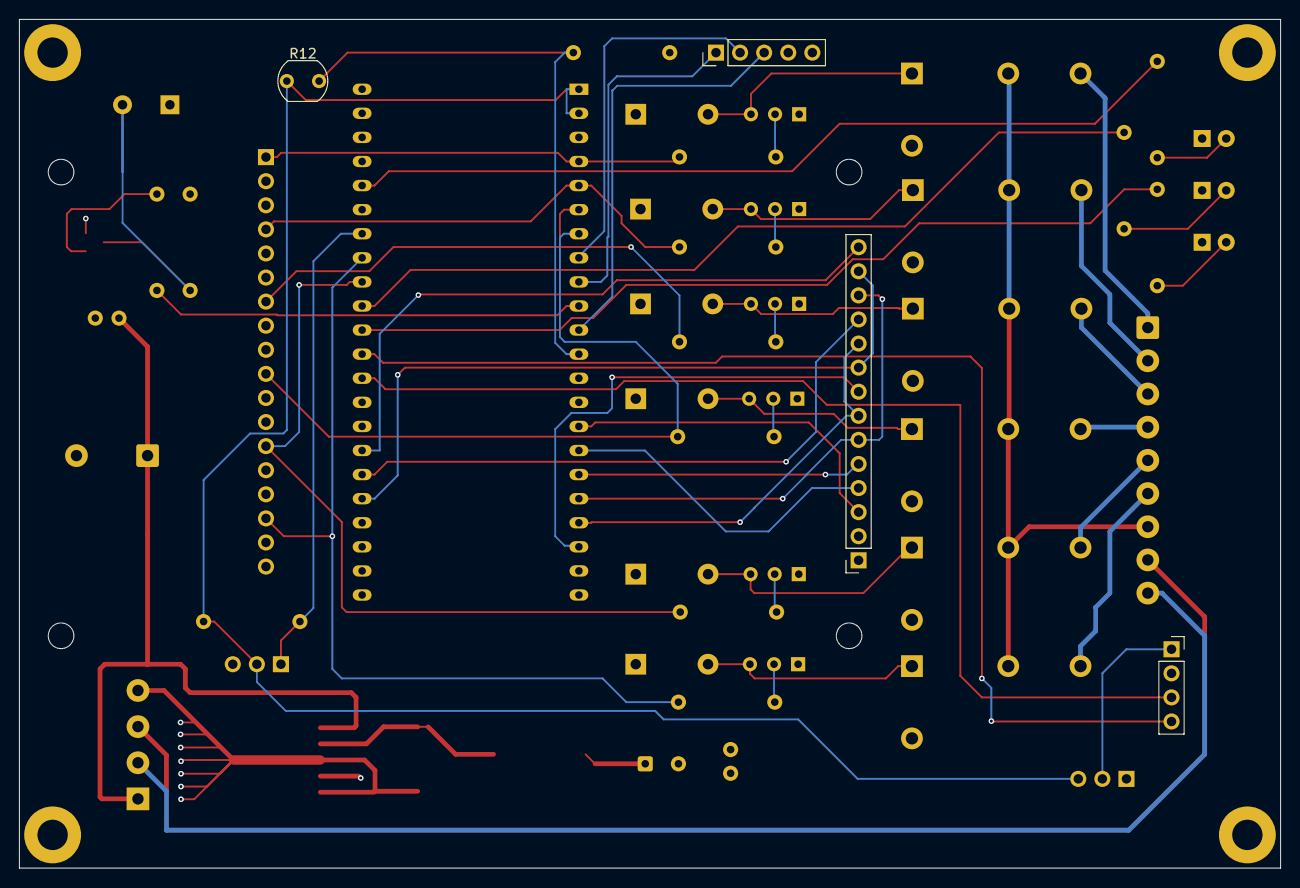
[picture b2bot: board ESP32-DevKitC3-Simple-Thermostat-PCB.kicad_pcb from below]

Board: 4 copper layers, 133.0 x 89.5 mm, 61 parts (4 on the bottom side), 58 nets.

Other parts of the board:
H1, H2, H3, H4: MountingHole_M3_3.2mm_Pad; MountingHole_3.2mm_Pad
H5, H6, H7, H8: MountingHole; MountingHole_2.7mm_M2.5

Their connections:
GND: H1.1, H2.1, H3.1, H4.1; also elsewhere on the board

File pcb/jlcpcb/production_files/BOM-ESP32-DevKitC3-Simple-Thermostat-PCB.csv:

Comment,Designator,Footprint,LCSC,Quantity
1000uF_50V,C5,CP_Radial_D16.0mm_P7.50mm,C445418,1
100nF_Ceramic,"C6,C9",C_Disc_D5.0mm_W2.5mm_P2.50mm,C1517817,2
10k,"R10,R9",R_Axial_DIN0207_L6.3mm_D2.5mm_P10.16mm_Horizontal,C119347,2
12uH_5.2A_1260,L1,L_Bourns_SRR1260,C2041353,1
1N4007,"D1,D2,D3,D4,D5,D6",D_DO-41_SOD81_P7.62mm_Horizontal,C2457,6
1k,"R11,R13,R14,R8",R_Axial_DIN0207_L6.3mm_D2.5mm_P10.16mm_Horizontal,C119324,4
2N2222A-TO92,"Q1,Q2,Q3,Q4,Q5,Q6",TO-92_Inline_Wide_EBC,C118536,6
2N7002,Q7,SOT-23,C8545,1
3.2 lcd tft,J4,PinSocket_1x14_P2.54mm_Vertical,C49569750,1
4.7k,"R1,R2,R3,R4,R5,R6,R7",R_Axial_DIN0207_L6.3mm_D2.5mm_P10.16mm_Horizontal,C119339,7
470uF_10V,C8,CP_Radial_D8.0mm_P3.50mm,C3274796,1
Buzzer,BZ1,Buzzer_TDK_PS1240P02BT_D12.2mm_H6.5mm,C76871,1
COOL,D11,LED_D3.0mm,C17304835,1
DS18B20,J3,PinHeader_1x03_P2.54mm_Vertical,C2932698,1
FAN,D9,LED_D3.0mm,C17340814,1
G5Q-1A,"K1,K2,K3,K4,K5,K6",Relay_SPST_Omron-G5Q-1A,C5204063,6
HEAT,D10,LED_D3.0mm,C5990731,1
KBP210G,D7,Diode_Bridge_KBP,C244333,1
LM2596S-5,U2,TO-263-5_TabPin3,C347445,1
PINHD_1x18_Male,J1,PinHeader_1x18_P2.54mm_Vertical,C27985197,1
PINHD_1x3_Male,J7,PinHeader_1x03_P2.54mm_Vertical,C2932698,1
SS34,D8,D_SMC,C908239,1
Screw_Terminal_9_P3.50mm,J2,"TerminalBlock_Phoenix_PT-1,5-9-3.5-H_1x09_P3.50mm_Horizontal",C6373199,1
MountingHole_M3_3.2mm_Pad,H3,MountingHole_3.2mm_Pad,,1
MountingHole_M3_3.2mm_Pad,H2,MountingHole_3.2mm_Pad,,1
MountingHole_M3_3.2mm_Pad,H1,MountingHole_3.2mm_Pad,,1
MountingHole_M3_3.2mm_Pad,H4,MountingHole_3.2mm_Pad,,1

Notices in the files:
README.md:
📄 License:
This project is released under the GNU General Public License v3.0. Free to use, modify, and distribute. NOT for commercial use.
